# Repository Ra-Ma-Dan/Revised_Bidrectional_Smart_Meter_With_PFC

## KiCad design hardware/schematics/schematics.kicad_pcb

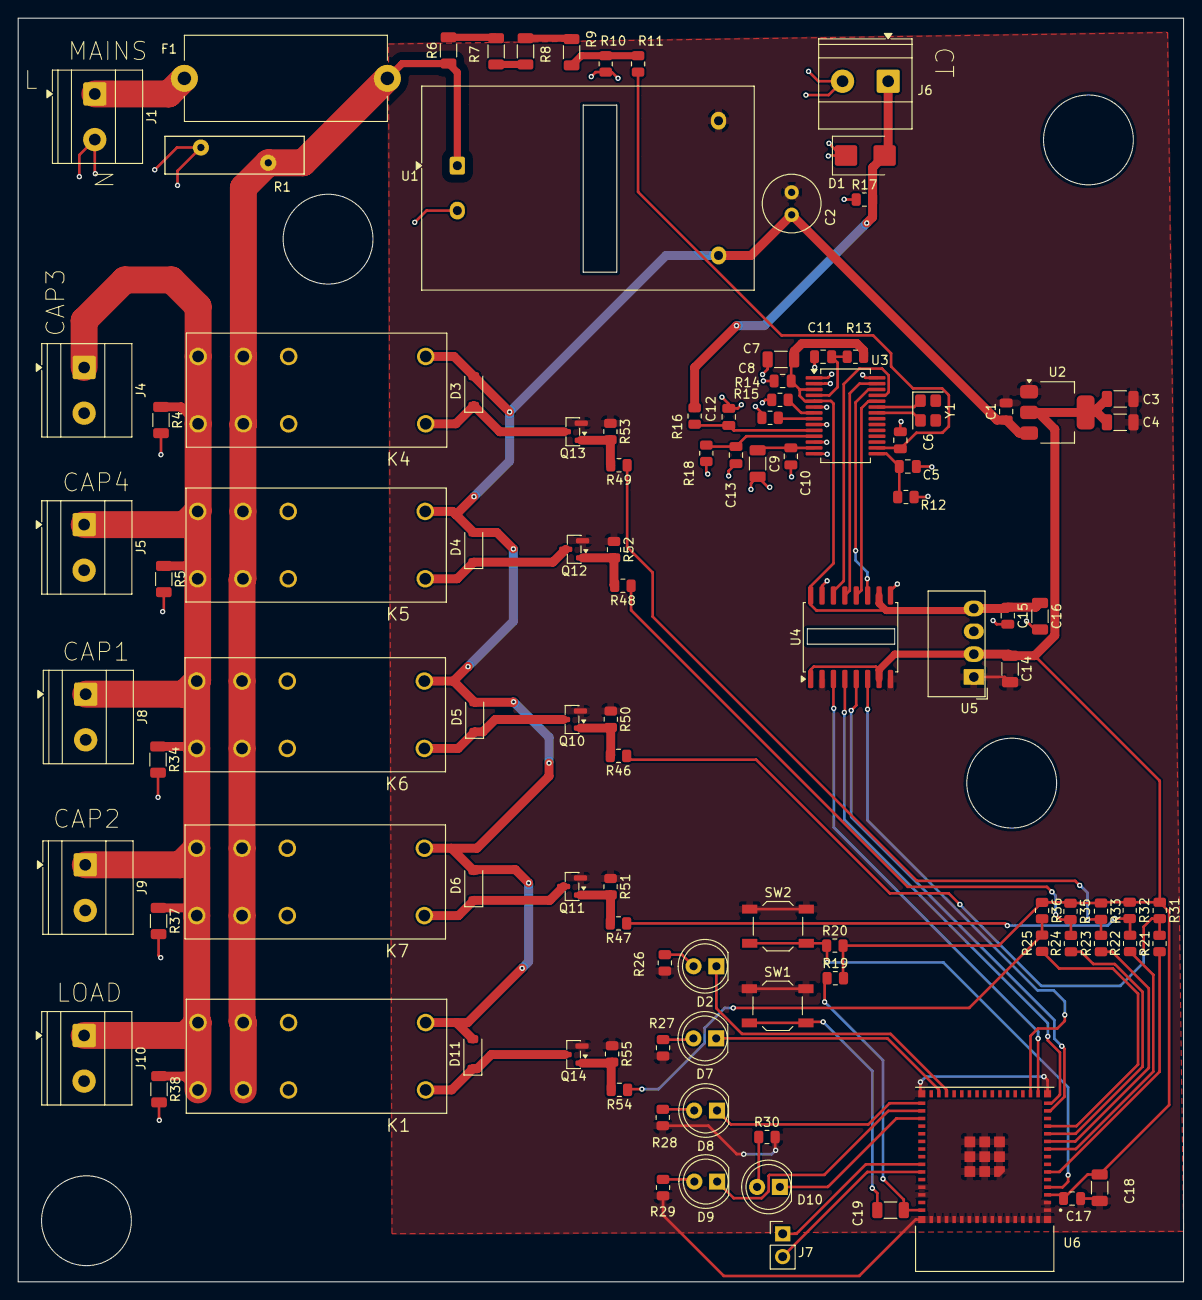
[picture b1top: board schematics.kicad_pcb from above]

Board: 2 copper layers, 129.7 x 140.7 mm, 104 parts (0 on the bottom side), 66 nets.

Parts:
C1: 10uF(cera); C_0805_2012Metric
C2: 100uF/16V; C_Radial_D6.3mm_H11.0mm_P2.50mm
C3: 100nF; C_1206_3216Metric
C4: 22uF; C_1206_3216Metric
C5, C6, C12, C13: 33nF; C_0805_2012Metric
C7, C9, C14, C16, C18, C19: 10uF; C_1206_3216Metric
C8, C10, C11, C15, C17: 100nF; C_0805_2012Metric
D1: D_TVS; D_SMB
D2, D7, D8, D9, D10: LED; LED_D5.0mm
D3, D4, D5, D6, D11: 1N4148W; D_SOD-123
F1: Fuse; Fuseholder_Cylinder-5x20mm_Stelvio-Kontek_PTF78_Horizontal_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
J1, J4, J5, J6, J8, J9, J10: Screw_Terminal_01x02; TerminalBlock_Phoenix_MKDS-1,5-2-5.08_1x02_P5.08mm_Horizont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
J7: Conn_01x02_Pin; PinHeader_1x02_P2.54mm_Vertical
K1, K4, K5, K6, K7: RTD14005; RELAY_RTD14005
Q10, Q11, Q12, Q13, Q14: AO3400A; SOT-23
R1: R_Variable; RV_Disc_D15.5mm_W4.2mm_P7.5mm
R4, R5, R34, R37, R38: 1M(0.5W); R_1206_3216Metric
R6, R7, R8, R9: 240K; R_1206_3216Metric
R10: 390R; R_0805_2012Metric
R11, R12, R14, R15, R16, R18: 1K; R_0805_2012Metric
R13, R19, R20, R50, R51, R52, R53, R55: 10K; R_0805_2012Metric
R17: 0R5; R_0805_2012Metric
R21, R22, R23, R24, R25, R46, R47, R48, R49, R54: 100R; R_0805_2012Metric
R26, R27, R28, R29, R30, R31, R32, R33, R35, R36: 330R; R_0805_2012Metric
SW1, SW2: SW_Push; SW_SPST_TL3342
U1: HLK-5M05; Converter_ACDC_Hi-Link_HLK-PMxx
U2: AMS1117; SOT-223-3_TabPin2
U3: ATM90E26-YU; SSOP-28_5.3x10.2mm_P0.65mm
U4: ADuM1401xRW; SOIC-16W_7.5x10.3mm_P1.27mm
U5: B0303S-1WR3; Converter_DCDC_Murata_MEE1SxxxxSC_THT
U6: ESP32-S3-MINI-1-N4R2; XCVR_ESP32-S3-MINI-1-N4R2
Y1: 8.192MHz; Crystal_SMD_3225-4Pin_3.2x2.5mm

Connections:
+3V3_HOT: C7.1, C8.1, C15.1, C16.1, R13.2, U3.3 (DVDD), U3.5 (AVDD), U4.10 (VE2), U4.16 (VDD2), U5.4 (+Vout)
+3V3_SELV: C3.1, C4.1, C14.1, C17.1, C18.1, R19.2, R20.2, R31.1, R32.1, R33.1, R35.1, R36.1, U2.2 (VO), U4.1 (VDD1), U4.7 (VE1), U5.2 (+Vin), U6.3 (3V3)
+5V_SELV: C1.1, C2.1, D3.2 (A), D4.2 (A), D5.2 (A), D6.2 (A), D11.2 (A), K1.A1, K4.A1, K5.A1, K6.A1, K7.A1, U1.4 (+Vout), U2.3 (VI)
/ATM90E26_AFE/CT_P: D1.2 (A2), J6.1, R16.2, R17.2
/ESP32_and_Relay_Drivers/LED_APFC_Active: D8.1 (K), U6.31 (IO35)
/ESP32_and_Relay_Drivers/LED_Fault: D9.1 (K), U6.32 (IO36)
/ESP32_and_Relay_Drivers/LED_Metering_Active: D10.1 (K), U6.33 (IO37)
/ESP32_and_Relay_Drivers/LED_Power: D7.1 (K), U6.29 (IO34)
/ESP32_and_Relay_Drivers/LED_WiFi: D2.1 (K), U6.28 (IO33)
GND_HOT: C5.2, C6.2, C7.2, C8.2, C9.2, C10.2, C11.2, C12.2, C13.2, C15.2, C16.2, D1.1 (A1), J1.2, J4.2, J5.2, J6.2, J8.2, J9.2, J10.2, R1.2, R4.2, R5.2, R10.2, R12.2, R14.2, R15.2, R17.1, R18.2, R34.2, R37.2, R38.2, U1.2 (AC/N), U3.1 (MMD1), U3.2 (DGND), U3.6 (AGND), U3.9 (DGND), U3.12 (USEL), U3.14 (AGND), U3.28 (MMD0), U4.9 (GND2), U4.15 (GND2), U5.3 (-Vout)
GND_SELV: C1.2, C2.2, C3.2, C4.2, C14.2, C17.2, C18.2, Q10.2 (S), Q11.2 (S), Q12.2 (S), Q13.2 (S), Q14.2 (S), R26.2, R27.2, R28.2, R29.2, R30.2, R50.1, R51.1, R52.1, R53.1, R55.1, SW1.1, SW2.1, U1.3 (-Vout), U2.1 (ADJ), U4.2 (GND1), U4.8 (GND1), U5.1 (-Vin), U6.1 (GND), U6.2 (GND), U6.42 (GND), U6.43 (GND), U6.46 (GND), U6.47 (GND), U6.48 (GND), U6.49 (GND), U6.50 (GND), U6.51 (GND), U6.52 (GND), U6.53 (GND), U6.54 (GND), U6.55 (GND), U6.56 (GND), U6.57 (GND), U6.58 (GND), U6.59 (GND), U6.60 (GND), U6.61 (GND), U6.61_1 (GND), U6.61_2 (GND), U6.61_3 (GND), U6.61_4 (GND), U6.61_5 (GND), U6.61_6 (GND), U6.61_7 (GND), U6.61_8 (GND), U6.62 (GND), U6.63 (GND), U6.64 (GND), U6.65 (GND)
MAINS_L: F1.1, J1.1
MAINS_L_FUSED: F1.2, K1.1, K1.11, K4.1, K4.11, K5.1, K5.11, K6.1, K6.11, K7.1, K7.11, R1.1, R6.1, U1.1 (AC/L)
MAIN_RELAY_DRV: D11.1 (K), K1.A2, Q14.3 (D)
MAIN_RELAY_PIN: R25.2, R36.2, R54.1
unnamed: C19.2, SW1.2
unnamed: D2.2 (A), R26.1
unnamed: D7.2 (A), R27.1
unnamed: D8.2 (A), R28.1
unnamed: D9.2 (A), R29.1
unnamed: D10.2 (A), R30.1
unnamed: J7.1, U6.39 (TXD0)
unnamed: J7.2, U6.40 (RXD0)
unnamed: Q10.1 (G), R46.2, R50.2
unnamed: Q11.1 (G), R47.2, R51.2
unnamed: Q12.1 (G), R48.2, R52.2
unnamed: Q13.1 (G), R49.2, R53.2
unnamed: Q14.1 (G), R54.2, R55.2
unnamed: R6.2, R7.1
unnamed: R7.2, R8.1
unnamed: R8.2, R9.1
unnamed: R9.2, R10.1, R11.2
unnamed: C13.1, R18.1, U3.11 (I1N)
unnamed: C12.1, R16.1, U3.10 (I1P)
unnamed: R15.1, U3.8 (I2N)
unnamed: R14.1, U3.7 (I2P)
unnamed: U3.22 (OSCI), Y1.2
unnamed: U3.23 (OSCO), Y1.1
unnamed: C5.1, R12.1, U3.15 (VN)
unnamed: C6.1, R11.1, U3.16 (VP)
unnamed: C9.1, C10.1, U3.13 (Vref)
unnamed: C11.1, R13.1, U3.4 (~Reset)
unnamed: C19.1, R19.1, U6.45 (EN)
unnamed: R20.1, SW2.2, U6.4 (IO0)
unnamed: R21.1, U6.6 (IO2)
unnamed: R22.1, U6.9 (IO5)
unnamed: R23.1, U6.10 (IO6)
unnamed: R24.1, U6.11 (IO7)
unnamed: R25.1, U6.12 (IO8)
RELAY_1_DRV: D5.1 (K), K6.A2, Q10.3 (D)
RELAY_1_PIN: R21.2, R31.2, R46.1
RELAY_2_DRV: D6.1 (K), K7.A2, Q11.3 (D)
RELAY_2_PIN: R22.2, R32.2, R47.1
RELAY_3_DRV: D3.1 (K), K4.A2, Q13.3 (D)
RELAY_3_PIN: R23.2, R33.2, R49.1
RELAY_4_DRV: D4.1 (K), K5.A2, Q12.3 (D)
RELAY_4_PIN: R24.2, R35.2, R48.1
SPI_CS_HOT: U3.24 (~CS), U4.12 (VOC)
SPI_CS_SELV: U4.5 (VIC), U6.14 (IO10)
SPI_MISO_HOT: U3.26 (SDO/UTX), U4.11 (VID)
SPI_MISO_SELV: U4.6 (VOD), U6.17 (IO13)
SPI_MOSI_HOT: U3.27 (SDI/URX), U4.13 (VOB)
SPI_MOSI_SELV: U4.4 (VIB), U6.15 (IO11)
SPI_SCLK_HOT: U3.25 (SCLK), U4.14 (VOA)
SPI_SCLK_SELV: U4.3 (VIA), U6.16 (IO12)
caps_terminal_L: J4.1, J5.1, J8.1, J9.1, J10.1, K1.4, K1.14, K4.4, K4.14, K5.4, K5.14, K6.4, K6.14, K7.4, K7.14, R4.1, R5.1, R34.1, R37.1, R38.1

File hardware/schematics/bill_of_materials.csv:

"Id";"Designator";"Footprint";"Quantity";"Designation";"Supplier and ref";
1;"C1";"C_0805_2012Metric";1;"10uF(cera)";;;
2;"C2";"C_Radial_D6.3mm_H11.0mm_P2.50mm";1;"100uF/16V";;;
3;"C3";"C_1206_3216Metric";1;"100nF";;;
4;"C4";"C_1206_3216Metric";1;"22uF";;;
5;"C5, C6, C12, C13";"C_0805_2012Metric";4;"33nF";;;
6;"C7, C9, C14, C16, C18, C19";"C_1206_3216Metric";6;"10uF";;;
7;"C8, C10, C11, C15, C17";"C_0805_2012Metric";5;"100nF";;;
8;"D1";"D_SMB";1;"D_TVS";;;
9;"D2, D7, D8, D9, D10";"LED_D5.0mm";5;"LED";;;
10;"D3, D4, D5, D6, D11";"D_SOD-123";5;"1N4148W";;;
11;"F1";"Fuseholder_Cylinder-5x20mm_Stelvio-Kontek_PTF78_Horizontal_Open";1;"Fuse";;;
12;"J1, J4, J5, J6, J8, J9, J10";"TerminalBlock_Phoenix_MKDS-1,5-2-5.08_1x02_P5.08mm_Horizontal";7;"Screw_Terminal_01x02";;;
13;"J7";"PinHeader_1x02_P2.54mm_Vertical";1;"Conn_01x02_Pin";;;
14;"K1, K4, K5, K6, K7";"RELAY_RTD14005";5;"RTD14005";;;
15;"Q10, Q11, Q12, Q13, Q14";"SOT-23";5;"AO3400A";;;
16;"R1";"RV_Disc_D15.5mm_W4.2mm_P7.5mm";1;"R_Variable";;;
17;"R4, R5, R34, R37, R38";"R_1206_3216Metric";5;"1M(0.5W)";;;
18;"R6, R7, R8, R9";"R_1206_3216Metric";4;"240K";;;
19;"R10";"R_0805_2012Metric";1;"390R";;;
20;"R11, R12, R14, R15, R16, R18";"R_0805_2012Metric";6;"1K";;;
21;"R13, R19, R20, R50, R51, R52, R53, R55";"R_0805_2012Metric";8;"10K";;;
22;"R17";"R_0805_2012Metric";1;"0R5";;;
23;"R21, R22, R23, R24, R25, R46, R47, R48, R49, R54";"R_0805_2012Metric";10;"100R";;;
24;"R26, R27, R28, R29, R30, R31, R32, R33, R35, R36";"R_0805_2012Metric";10;"330R";;;
25;"SW1, SW2";"SW_SPST_TL3342";2;"SW_Push";;;
26;"U1";"Converter_ACDC_Hi-Link_HLK-PMxx";1;"HLK-5M05";;;
27;"U2";"SOT-223-3_TabPin2";1;"AMS1117";;;
28;"U3";"SSOP-28_5.3x10.2mm_P0.65mm";1;"ATM90E26-YU";;;
29;"U4";"SOIC-16W_7.5x10.3mm_P1.27mm";1;"ADuM1401xRW";;;
30;"U5";"Converter_DCDC_Murata_MEE1SxxxxSC_THT";1;"B0303S-1WR3";;;
31;"U6";"XCVR_ESP32-S3-MINI-1-N4R2";1;"ESP32-S3-MINI-1-N4R2";;;
32;"Y1";"Crystal_SMD_3225-4Pin_3.2x2.5mm";1;"8.192MHz";;;
